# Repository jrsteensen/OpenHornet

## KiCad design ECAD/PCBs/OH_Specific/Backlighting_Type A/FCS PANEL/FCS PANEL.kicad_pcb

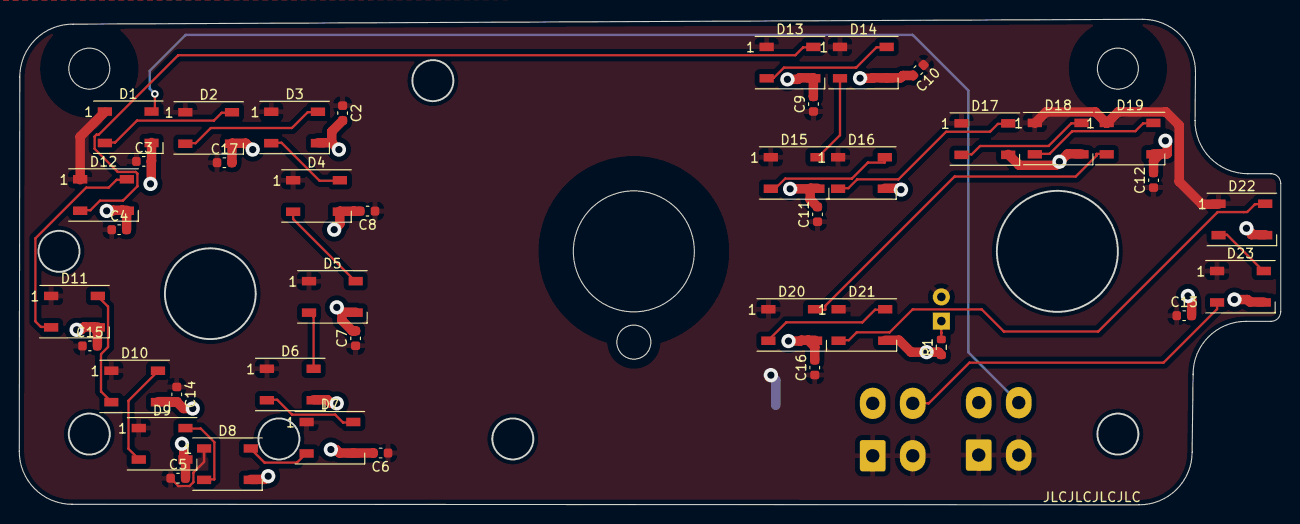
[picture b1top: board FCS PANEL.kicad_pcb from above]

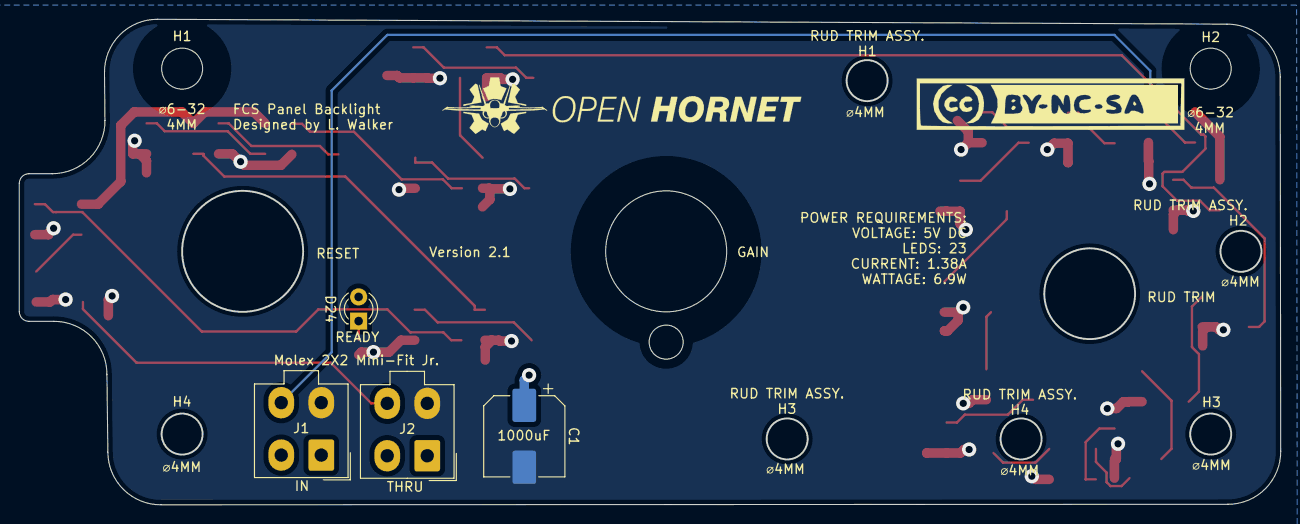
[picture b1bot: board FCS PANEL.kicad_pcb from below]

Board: 2 copper layers, 132.4 x 51.0 mm, 47 parts (4 on the bottom side), 27 nets.

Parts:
1: 100SPX_Toggle_13mm_x_18mm
1#2, 2: OH_Panel_Fastner_Keepout; OH_Panel_6-32_PHS
C1: C_Polarized; CP_Elec_8x10
C2, C3, C4, C5, C6, C7, C8, C9, C10, C11, C12, C13, C14, C15, C16, C17: C; C_0603_1608Metric
D1, D2, D3, D4, D5, D6, D7, D8, D9, D10, D11, D12, D13, D14, D15, D16, D17, D18, D19, D20, D21, D22, D23: WS2812B; LED_WS2812B_PLCC4_5.0x5.0mm_P3.2mm
D24: LED; LED_D3.0mm
J1, J2: Conn_01x04_Female; Molex_Mini-Fit_Jr_5566-04A_2x02_P4.20mm_Vertical
R1: R; R_0603_1608Metric

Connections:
/DATAIN: D1.4 (DIN), J1.4
/DATAOUT: D23.2 (DOUT), J2.4
/LED+5V: C1.1, C2.1, C3.1, C4.1, C5.1, C6.1, C7.1, C8.1, C9.1, C10.1, C11.1, C12.1, C13.1, C14.1, C15.1, C16.1, C17.1, D1.1 (VDD), D2.1 (VDD), D3.1 (VDD), D4.1 (VDD), D5.1 (VDD), D6.1 (VDD), D7.1 (VDD), D8.1 (VDD), D9.1 (VDD), D10.1 (VDD), D11.1 (VDD), D12.1 (VDD), D13.1 (VDD), D14.1 (VDD), D15.1 (VDD), D16.1 (VDD), D17.1 (VDD), D18.1 (VDD), D19.1 (VDD), D20.1 (VDD), D21.1 (VDD), D22.1 (VDD), D23.1 (VDD), D24.2 (A), J1.1, J1.2, J2.1, J2.2
/LEDGND: C1.2, C2.2, C3.2, C4.2, C5.2, C6.2, C7.2, C8.2, C9.2, C10.2, C11.2, C12.2, C13.2, C14.2, C15.2, C16.2, C17.2, D1.3 (VSS), D2.3 (VSS), D3.3 (VSS), D4.3 (VSS), D5.3 (VSS), D6.3 (VSS), D7.3 (VSS), D8.3 (VSS), D9.3 (VSS), D10.3 (VSS), D11.3 (VSS), D12.3 (VSS), D13.3 (VSS), D14.3 (VSS), D15.3 (VSS), D16.3 (VSS), D17.3 (VSS), D18.3 (VSS), D19.3 (VSS), D20.3 (VSS), D21.3 (VSS), D22.3 (VSS), D23.3 (VSS), J1.3, J2.3, R1.1
unnamed: D1.2 (DOUT), D2.4 (DIN)
unnamed: D2.2 (DOUT), D3.4 (DIN)
unnamed: D3.2 (DOUT), D4.4 (DIN)
unnamed: D4.2 (DOUT), D5.4 (DIN)
unnamed: D5.2 (DOUT), D6.4 (DIN)
unnamed: D6.2 (DOUT), D7.4 (DIN)
unnamed: D7.2 (DOUT), D8.4 (DIN)
unnamed: D8.2 (DOUT), D9.4 (DIN)
unnamed: D10.2 (DOUT), D11.4 (DIN)
unnamed: D9.2 (DOUT), D10.4 (DIN)
unnamed: D11.2 (DOUT), D12.4 (DIN)
unnamed: D12.2 (DOUT), D13.4 (DIN)
unnamed: D13.2 (DOUT), D14.4 (DIN)
unnamed: D14.2 (DOUT), D15.4 (DIN)
unnamed: D15.2 (DOUT), D16.4 (DIN)
unnamed: D16.2 (DOUT), D17.4 (DIN)
unnamed: D17.2 (DOUT), D18.4 (DIN)
unnamed: D18.2 (DOUT), D19.4 (DIN)
unnamed: D19.2 (DOUT), D20.4 (DIN)
unnamed: D20.2 (DOUT), D21.4 (DIN)
unnamed: D21.2 (DOUT), D22.4 (DIN)
unnamed: D22.2 (DOUT), D23.4 (DIN)
unnamed: D24.1 (K), R1.2

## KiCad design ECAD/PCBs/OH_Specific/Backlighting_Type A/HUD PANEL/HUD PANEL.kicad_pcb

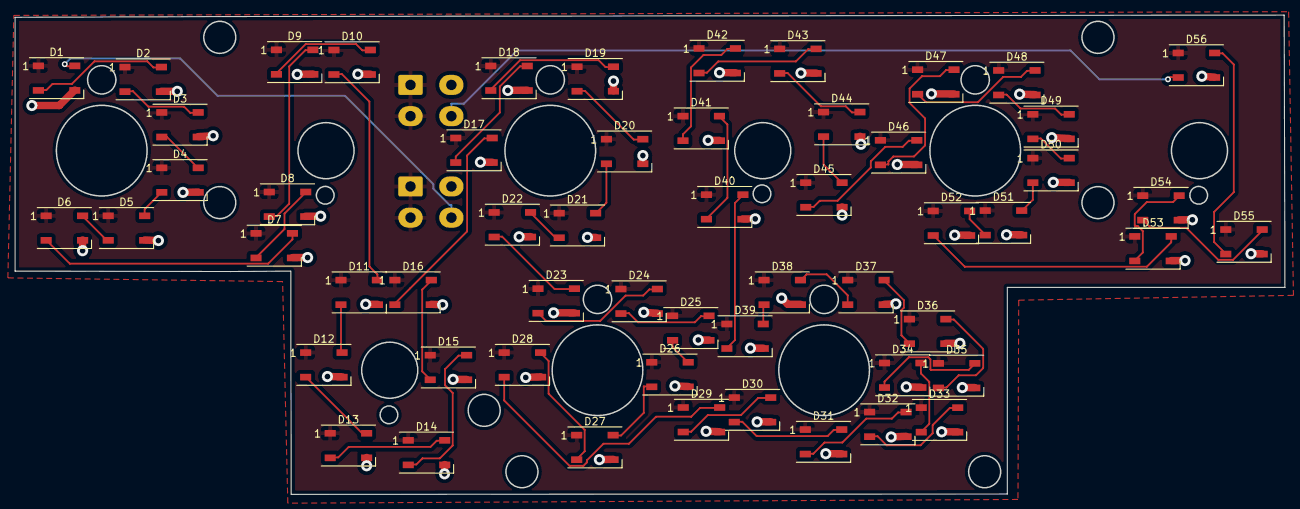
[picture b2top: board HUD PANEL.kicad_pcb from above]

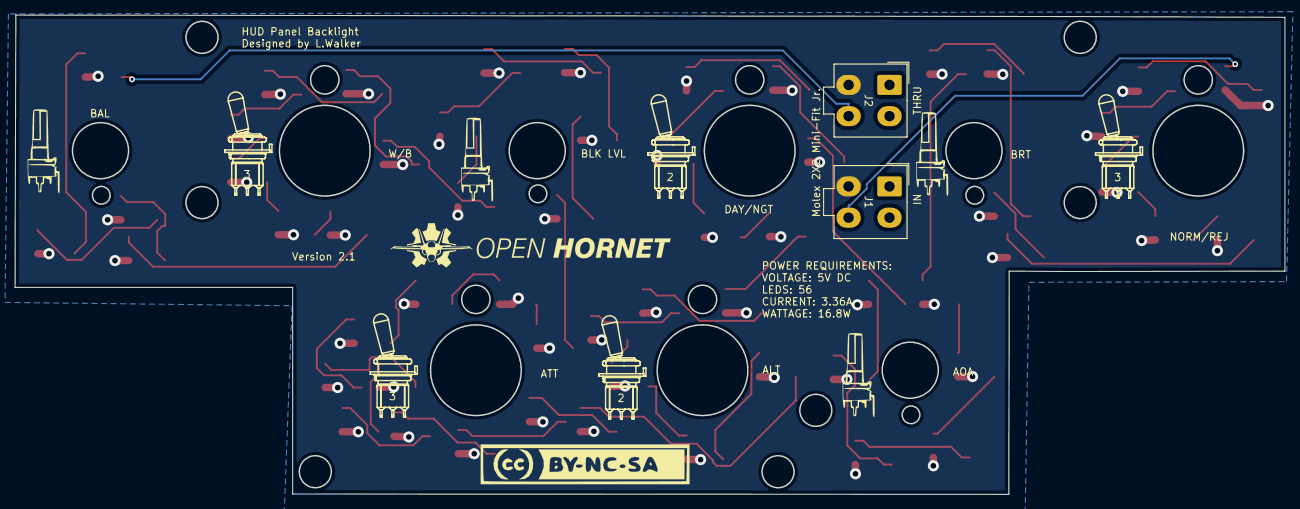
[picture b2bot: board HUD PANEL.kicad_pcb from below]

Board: 2 copper layers, 170.8 x 64.5 mm, 62 parts (2 on the bottom side), 59 nets.

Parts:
D1, D2, D3, D4, D5, D6, D7, D8, D9, D10, D11, D12, D13, D14, D15, D16, D17, D18, D19, D20, D21, D22, D23, D24, D25, D26, D27, D28, D29, D30, D31, D32, D33, D34, D35, D36, D37, D38, D39, D40, D41, D42, D43, D44, D45, D46, D47, D48, D49, D50, D51, D52, D53, D54, D55, D56: WS2812B; LED_WS2812B_PLCC4_5.0x5.0mm_P3.2mm
J1, J2: Conn_01x04_Female; Molex_Mini-Fit_Jr_5566-04A_2x02_P4.20mm_Vertical
LOGO1, LOGO3, LOGO4, LOGO6: OH_BR10KPot_Silkscreen; BR10K_Pot_Silkscreen

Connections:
/DATAIN: D1.4 (DIN), J1.4
/DATAOUT: D56.2 (DOUT), J2.4
/LED+5V: D1.1 (VDD), D2.1 (VDD), D3.1 (VDD), D4.1 (VDD), D5.1 (VDD), D6.1 (VDD), D7.1 (VDD), D8.1 (VDD), D9.1 (VDD), D10.1 (VDD), D11.1 (VDD), D12.1 (VDD), D13.1 (VDD), D14.1 (VDD), D15.1 (VDD), D16.1 (VDD), D17.1 (VDD), D18.1 (VDD), D19.1 (VDD), D20.1 (VDD), D21.1 (VDD), D22.1 (VDD), D23.1 (VDD), D24.1 (VDD), D25.1 (VDD), D26.1 (VDD), D27.1 (VDD), D28.1 (VDD), D29.1 (VDD), D30.1 (VDD), D31.1 (VDD), D32.1 (VDD), D33.1 (VDD), D34.1 (VDD), D35.1 (VDD), D36.1 (VDD), D37.1 (VDD), D38.1 (VDD), D39.1 (VDD), D40.1 (VDD), D41.1 (VDD), D42.1 (VDD), D43.1 (VDD), D44.1 (VDD), D45.1 (VDD), D46.1 (VDD), D47.1 (VDD), D48.1 (VDD), D49.1 (VDD), D50.1 (VDD), D51.1 (VDD), D52.1 (VDD), D53.1 (VDD), D54.1 (VDD), D55.1 (VDD), D56.1 (VDD), J1.1, J1.2, J2.1, J2.2
/LEDGND: D1.3 (VSS), D2.3 (VSS), D3.3 (VSS), D4.3 (VSS), D5.3 (VSS), D6.3 (VSS), D7.3 (VSS), D8.3 (VSS), D9.3 (VSS), D10.3 (VSS), D11.3 (VSS), D12.3 (VSS), D13.3 (VSS), D14.3 (VSS), D15.3 (VSS), D16.3 (VSS), D17.3 (VSS), D18.3 (VSS), D19.3 (VSS), D20.3 (VSS), D21.3 (VSS), D22.3 (VSS), D23.3 (VSS), D24.3 (VSS), D25.3 (VSS), D26.3 (VSS), D27.3 (VSS), D28.3 (VSS), D29.3 (VSS), D30.3 (VSS), D31.3 (VSS), D32.3 (VSS), D33.3 (VSS), D34.3 (VSS), D35.3 (VSS), D36.3 (VSS), D37.3 (VSS), D38.3 (VSS), D39.3 (VSS), D40.3 (VSS), D41.3 (VSS), D42.3 (VSS), D43.3 (VSS), D44.3 (VSS), D45.3 (VSS), D46.3 (VSS), D47.3 (VSS), D48.3 (VSS), D49.3 (VSS), D50.3 (VSS), D51.3 (VSS), D52.3 (VSS), D53.3 (VSS), D54.3 (VSS), D55.3 (VSS), D56.3 (VSS), J1.3, J2.3
unnamed: D1.2 (DOUT), D2.4 (DIN)
unnamed: D2.2 (DOUT), D3.4 (DIN)
unnamed: D3.2 (DOUT), D4.4 (DIN)
unnamed: D4.2 (DOUT), D5.4 (DIN)
unnamed: D5.2 (DOUT), D6.4 (DIN)
unnamed: D6.2 (DOUT), D7.4 (DIN)
unnamed: D7.2 (DOUT), D8.4 (DIN)
unnamed: D8.2 (DOUT), D9.4 (DIN)
unnamed: D10.2 (DOUT), D11.4 (DIN)
unnamed: D9.2 (DOUT), D10.4 (DIN)
unnamed: D11.2 (DOUT), D12.4 (DIN)
unnamed: D12.2 (DOUT), D13.4 (DIN)
unnamed: D13.2 (DOUT), D14.4 (DIN)
unnamed: D14.2 (DOUT), D15.4 (DIN)
unnamed: D15.2 (DOUT), D16.4 (DIN)
unnamed: D16.2 (DOUT), D17.4 (DIN)
unnamed: D17.2 (DOUT), D18.4 (DIN)
unnamed: D18.2 (DOUT), D19.4 (DIN)
unnamed: D19.2 (DOUT), D20.4 (DIN)
unnamed: D20.2 (DOUT), D21.4 (DIN)
unnamed: D21.2 (DOUT), D22.4 (DIN)
unnamed: D22.2 (DOUT), D23.4 (DIN)
unnamed: D23.2 (DOUT), D24.4 (DIN)
unnamed: D24.2 (DOUT), D25.4 (DIN)
unnamed: D25.2 (DOUT), D26.4 (DIN)
unnamed: D26.2 (DOUT), D27.4 (DIN)
unnamed: D27.2 (DOUT), D28.4 (DIN)
unnamed: D28.2 (DOUT), D29.4 (DIN)
unnamed: D29.2 (DOUT), D30.4 (DIN)
unnamed: D30.2 (DOUT), D31.4 (DIN)
unnamed: D31.2 (DOUT), D32.4 (DIN)
unnamed: D32.2 (DOUT), D33.4 (DIN)
unnamed: D33.2 (DOUT), D34.4 (DIN)
unnamed: D34.2 (DOUT), D35.4 (DIN)
unnamed: D35.2 (DOUT), D36.4 (DIN)
unnamed: D36.2 (DOUT), D37.4 (DIN)
unnamed: D37.2 (DOUT), D38.4 (DIN)
unnamed: D38.2 (DOUT), D39.4 (DIN)
unnamed: D39.2 (DOUT), D40.4 (DIN)
unnamed: D40.2 (DOUT), D41.4 (DIN)
unnamed: D41.2 (DOUT), D42.4 (DIN)
unnamed: D42.2 (DOUT), D43.4 (DIN)
unnamed: D43.2 (DOUT), D44.4 (DIN)
unnamed: D44.2 (DOUT), D45.4 (DIN)
unnamed: D45.2 (DOUT), D46.4 (DIN)
unnamed: D46.2 (DOUT), D47.4 (DIN)
unnamed: D47.2 (DOUT), D48.4 (DIN)
unnamed: D48.2 (DOUT), D49.4 (DIN)
unnamed: D49.2 (DOUT), D50.4 (DIN)
unnamed: D50.2 (DOUT), D51.4 (DIN)
unnamed: D51.2 (DOUT), D52.4 (DIN)
unnamed: D52.2 (DOUT), D53.4 (DIN)
unnamed: D53.2 (DOUT), D54.4 (DIN)
unnamed: D54.2 (DOUT), D55.4 (DIN)
unnamed: D55.2 (DOUT), D56.4 (DIN)
